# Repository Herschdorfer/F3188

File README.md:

# F3188

## Notes

| CSR PIN | F3188 PIN | Notes |
| -------- | -------- |-------|
| RST# | RST |Reset pin needs min 2.4s low to shutdown the Chip. has a build in Pull-Up Resistor|
| VREGENABLE | POWER_EN |A high signal powers up the chip.|
|  |  |Its tolerant to the VBAT. Button should be connected to VBAT.|
|  |  |Can, after power up, be used for other things. Has a build in Pull-Down.|
| ? | VCC | Not sure if connected directly to a pin on the CSR8645 |
| VBAT | VBAT | seems to be direclty connected to VBAT |
| SPI_PCM# | SPI_PCM | High for SPI operation|
| | | LOW for PCM operation|

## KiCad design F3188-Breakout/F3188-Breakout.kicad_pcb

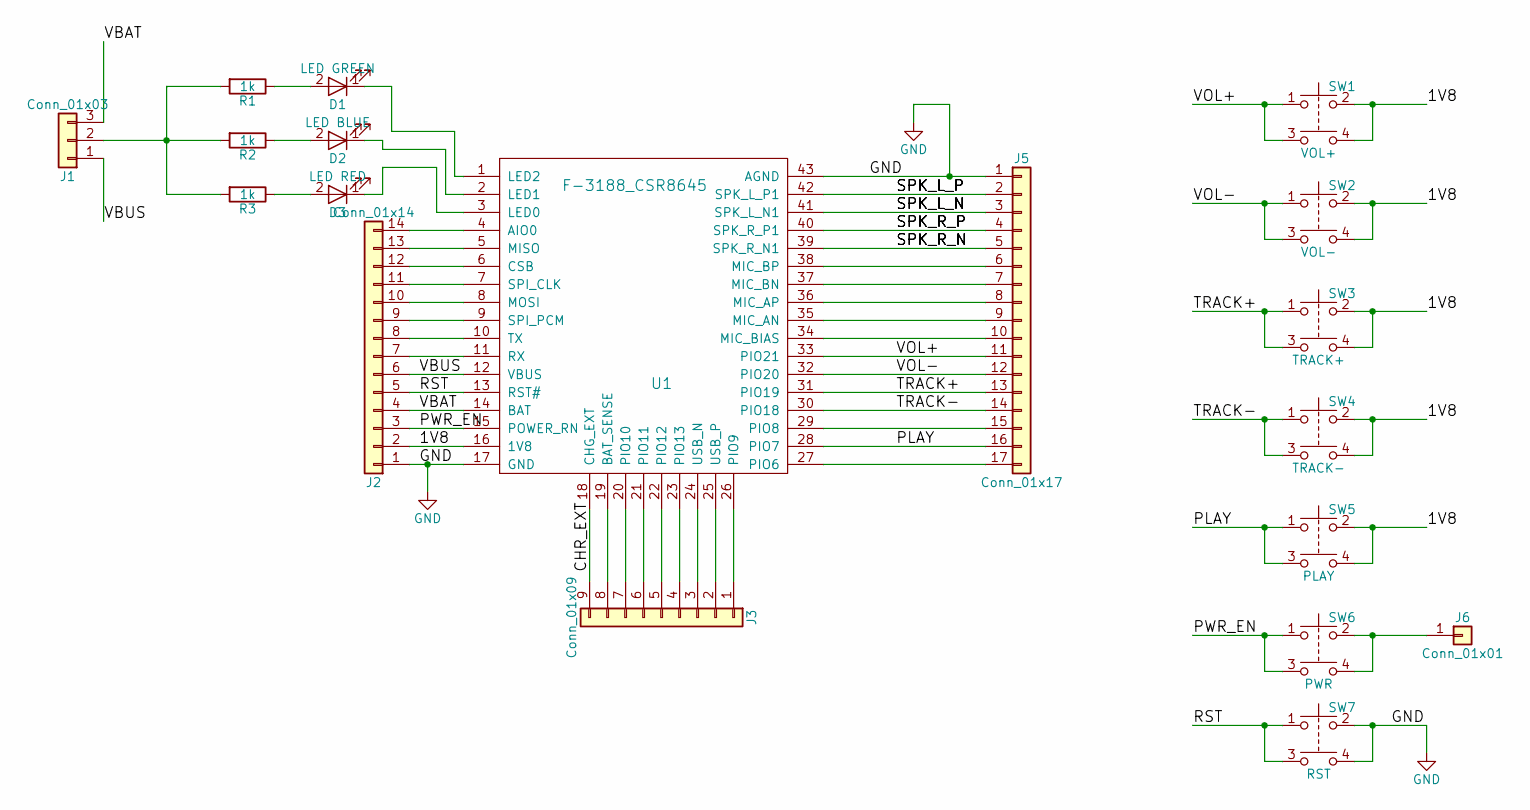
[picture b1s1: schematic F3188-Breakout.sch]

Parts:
D1: LED GREEN; LED_0805_HandSoldering
D2: LED BLUE; LED_0805_HandSoldering
D3: LED RED; LED_0805_HandSoldering
J1: Conn_01x03; Pin_Header_Straight_1x03_Pitch2.54mm
J2: Conn_01x14; Pin_Header_Straight_1x14_Pitch2.54mm
J3: Conn_01x09; Pin_Header_Straight_1x09_Pitch2.54mm
J5: Conn_01x17; Pin_Header_Straight_1x17_Pitch2.54mm
J6: Conn_01x01; Pin_Header_Straight_1x01_Pitch2.54mm
R1, R2, R3: 1k; R_0805_HandSoldering
SW1: VOL+; SW_TH_Tactile_Omron_B3F-10xx
SW2: VOL-; SW_TH_Tactile_Omron_B3F-10xx
SW3: TRACK+; SW_TH_Tactile_Omron_B3F-10xx
SW4: TRACK-; SW_TH_Tactile_Omron_B3F-10xx
SW5: PLAY; SW_TH_Tactile_Omron_B3F-10xx
SW6: PWR; SW_TH_Tactile_Omron_B3F-10xx
SW7: RST; SW_TH_Tactile_Omron_B3F-10xx
U1: F-3188_CSR8645

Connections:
/1V8: J2.2, SW1.2, SW1.4, SW2.2, SW2.4, SW3.2, SW3.4, SW4.2, SW4.4, SW5.2, SW5.4, U1.16 (1V8)
/CHR_EXT: J3.9, U1.18 (CHG_EXT)
/PLAY: J5.16, SW5.1, SW5.3, U1.28 (PIO7)
/PWR_EN: J2.3, SW6.1, SW6.3, U1.15 (POWER_RN)
/RST: J2.5, SW7.1, SW7.3, U1.13 (RST#)
/SPK_L_N: J5.3, U1.41 (SPK_L_N1)
/SPK_L_P: J5.2, U1.42 (SPK_L_P1)
/SPK_R_N: J5.5, U1.39 (SPK_R_N1)
/SPK_R_P: J5.4, U1.40 (SPK_R_P1)
/TRACK+: J5.13, SW3.1, SW3.3, U1.31 (PIO19)
/TRACK-: J5.14, SW4.1, SW4.3, U1.30 (PIO18)
/VBAT: J1.3, J2.4, U1.14 (BAT)
/VBUS: J1.1, J2.6, U1.12 (VBUS)
/VOL+: J5.11, SW1.1, SW1.3, U1.33 (PIO21)
/VOL-: J5.12, SW2.1, SW2.3, U1.32 (PIO20)
GND: J2.1, J5.1, SW7.2, SW7.4, U1.17 (GND), U1.43 (AGND)
unnamed: D1.1 (K), U1.1 (LED2)
unnamed: D1.2 (A), R1.1
unnamed: D2.1 (K), U1.2 (LED1)
unnamed: D2.2 (A), R2.1
unnamed: D3.1 (K), U1.3 (LED0)
unnamed: D3.2 (A), R3.1
unnamed: J1.2, R1.2, R2.2, R3.2
unnamed: J2.7, U1.11 (RX)
unnamed: J2.8, U1.10 (TX)
unnamed: J2.9, U1.9 (SPI_PCM)
unnamed: J2.10, U1.8 (MOSI)
unnamed: J2.11, U1.7 (SPI_CLK)
unnamed: J2.12, U1.6 (CSB)
unnamed: J2.13, U1.5 (MISO)
unnamed: J2.14, U1.4 (AIO0)
unnamed: J3.1, U1.26 (PIO9)
unnamed: J3.2, U1.25 (USB_P)
unnamed: J3.3, U1.24 (USB_N)
unnamed: J3.4, U1.23 (PIO13)
unnamed: J3.5, U1.22 (PIO12)
unnamed: J3.6, U1.21 (PIO11)
unnamed: J3.7, U1.20 (PIO10)
unnamed: J3.8, U1.19 (BAT_SENSE)
unnamed: J5.6, U1.38 (MIC_BP)
unnamed: J5.7, U1.37 (MIC_BN)
unnamed: J5.8, U1.36 (MIC_AP)
unnamed: J5.9, U1.35 (MIC_AN)
unnamed: J5.10, U1.34 (MIC_BIAS)
unnamed: J5.15, U1.29 (PIO8)
unnamed: J5.17, U1.27 (PIO6)
unnamed: J6.1, SW6.2, SW6.4

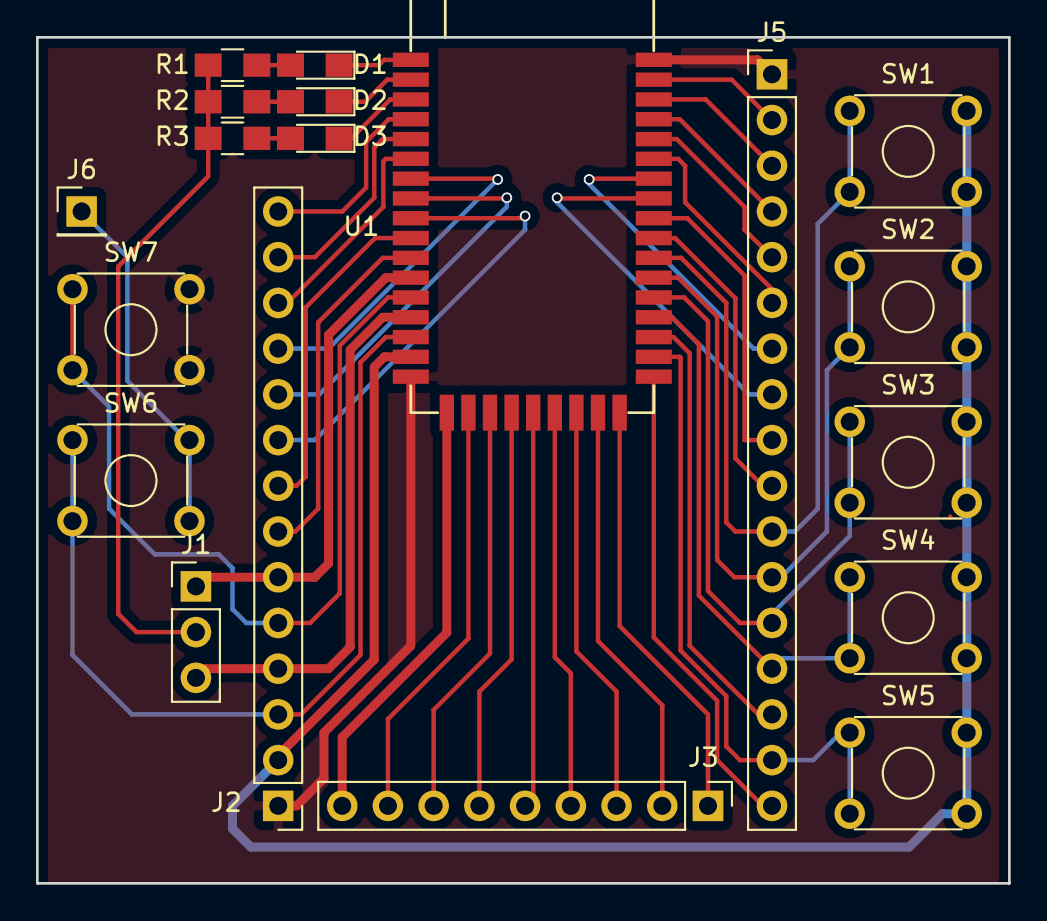
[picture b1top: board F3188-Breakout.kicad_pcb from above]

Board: 2 copper layers, 54.0 x 47.0 mm, 19 parts (0 on the bottom side), 47 nets.

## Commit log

2018-01-02 update doku
2018-05-05 added break out board
